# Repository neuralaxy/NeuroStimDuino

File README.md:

# NeuroStimDuino
An open source neurostimulator for students, researchers, and hobbyists interested in neuroscience

## Update for 2025 - NeuroStimDuino v3.0  launched!! :boom: :boom: 💫
Hello NeuroStim Enthusiats!! Its been a while....over the last year, we have been busy revising the design of NeuroStimDuino. The main reason for modifying NSDuino2.1 was that one of its crucial components, the high voltage DC-DC converter NMT0572SC from Murata has now became obsolete and out of circulation. Sadly, there was no alternative component that could take its place and we spend months trying to find a replacement. 

Finally we had a breakthrough, and we found another DC-DC converter IH0524 from XP Power. We had to redesign the board slightly to incorporate this Converter. But the *downside* is that the new converter only allows a compliance voltage of 35V instead of 60V available in the previous versions. How will this effect your experiments? Well, it means that now you will have to take extra effort in minimizing the skin impedance to deliver higher currents. But we have tried stimulating our arm muscles using this newer version, and it is just as effective as before. And we highly recommend using hydrogel electrodes, as we have suggested before in the [Zucchini](https://www.crowdsupply.com/neuralaxy/neurostimduino/updates/tips-on-electrode-placement) experiment. 

On the *upside*, while we were redesigning the board, we replaced the manual High Voltage slide switch with an electronic switch (see below). So now, you don't have to worry about turning ON the high voltage switch before activating the stimulator. Whenever you give the STIM command, the microcontroller will automatically turn ON the high voltage supply and once the stimulation is turned off, the high voltage supply is automatically turned off. Another benefit of adding the electronic switch is that it will minimize power consumption, since the high-voltage supply doesn't need to be always ON. Now that's smart😎.

All the other features from NSDuino2.1, like ramping stimulation intensity, touchproof conenctors, etc. have been carried over to NSDuino3.0. Late in September 2025, we launched NeuroStimDuino v3.0 abd shipped out the first batch to our distributor Mouser. A big shout out to 📢 CrowdSupply and Mouser for consistently supporting us over the years. Some of you might have already received the newer version. Try it and let us know how it goes.  

## Important update for 2023
In January 2023 we have launched NeuroStimDuino v2.1, which comes with additional features and improved functionality than its predecessor NeuroStimDuino v1.0. 

Here is a list of important upgrades for NeuroStimDuino v2.1 (NSDuino2.1): 
* Choosing between symmetrical and asymmetrical waveform shapes is now done entirely in software. In NeuroStimDuino v1.0, to switch from symmetrical to asymmetrical waveform, you had to change the jumper (J5, J6) as well as call the `SYMM` command. In NSDuino2.1, its handled entirely by software and the jumpers have been removed. In the default asymmetrical output mode, the anodic phase's amplitude is half of cathodic phase's amplitude and the duration of anodic phase is double that of the cathodic phase (to ensure charge balance). This ratio can be changed by modifying the firmware.

* NSDuino2.1's I<sup>2</sup>C address is now stored on EEPROM. So, whenever you assign a new I<sup>2</sup>C address to NSDuino2.1 using the `ADDR` command, it will get stored permanently and will be recalled at power-on reset. This is especially helpful when communicating with multiple NeuroStimDuinos. In NeuroStimDuino v1.0, the address would reset to the default value (0x1A) everytime the board was turned on and you would have to painstakingly re-assign the new addresses each time. With NSDuino2.1 the new address only needs to be set once and it will store it on-board its EEPROM.

* Many of NeuroStimDuino v1.0 users (who are acutally scientists!!) have asked whether it is possible to ramp up and down the stimulation intensity? Ramping is used in neurostimulation research to avoid painful sensations allow smoother transitions between movements when applying electrical stimulation. With NSDuino2.1, we have also expanded our software (Arduino) library and now provide the option to Ramp Up and Down the stimulation intentsity. When you enable ramping by using the command `RAMP 1`, the stimulation intensity will gradually increase from 0 to the desired level over a 1 second interval. At the end of stimulation, the stimulation intensity will gradually decrease to zero over a 1 second interval. There are some caveats to using ramping: 
  * In the scientific literature, ramping is usually done by increasing/decreasing the current amplitude. While this is doable, by changing the counts of our on-board digital potentiometer, it would require multiple SPI calls between the MCU and potentiometer which will introduce delays. Instead, we are performing ramping by gradually increasing the stimulation pulse-width. This is handled entirely by the MCU and hence it is more accurate. Additionally, it has the same effect as changing the stimulation current, so it won't affect the outcomes of your experiments. Refer to the below gif to understand how ramping essentially works:

  * Currently, ramping only works for finite stimulation intervals. This means the `Stim Indefinitely` flag of the `STIM` command must be set to `FALSE`. An example code snippet is as follows:
  
  ```
  RAMP 1          // Turn ON ramping on channels 1 & 2
  STIM 1 5 0      // Stimulate on channel 1 for 5 sec, stim indefinitely flag = 0
  RAMP 0          // Turn OFF ramping on channels 1 & 2
  ```
  * Ramping can also be deployed in NeuroStimDuino v1.0. This would require a firmware update. We will post an upgraded firmware for NeuroStimDuino v1.0 on our repository in a few weeks time. Feel free to reach out to us for any queries regarding ramping

* Additional minor modifications:
  * We removed the bi-color(red/green) LEDs to indicate when channels 1 and 2 are stimulating, with regular monocolor LEDs. These still function in the same way

  * We changed the onboard cable connectors for Channels 1 & 2 with new ones that are compatible with our stimulation cables and you no longer need to remove the cable shroud or sheath cover. This will hopefully help reduce the hassle during setup and the touchproof connectors will offer additional safety during use.

# Getting Started Tutorial for NeuroStimDuino v2.1
**_Important:_** For instructions on getting started with NeuroStimDuino v1.0, please click [here](https://github.com/neuralaxy/NeuroStimDuino/blob/main/NeuroStimDuino%20v1.0%20Getting%20Started.md#getting-started-tutorial-for-neurostimduino-v10)

* To get started, first and foremost familiarize yourself with NeuroStimDuino pinout and board layout below:

* If you have ordered the NeuroStimDuino board (without the accessory pack), then you will have received the following components.

* You also need to order a pair of hydrogel electrodes (from any retail vendor) if you plan to stimulate a fake muscle (such as a [Zucchini](https://www.crowdsupply.com/neuralaxy/neurostimduino/updates/tips-on-electrode-placement)) or for your research.

* Finally, before you begin, please remember to review the **safety guidelines** listed at the [end](https://github.com/neuralaxy/NeuroStimDuino/blob/main/README.md#important-safety-guidelines) of this tutorial and follow the recommendations mentioned therein.  

## Hardware Setup
* The battery holder included requires two 18650 Li-ion batteries (not included) to be connected in series. The battery holder allows the batteries to be oriented in series or parallel connection. Unfortunately, the battery holders we shipped only have Chinese labels to indicate the series or parallel oritentation. Make sure you connect the batteries in series (as shown below) and not in parallel. Alternately, you can power NeuroStimDuino using your own battery source between 6-20V. We do not recommend powering NeuroStimDuino using an AC-DC adapter. However, if you must use an adapter, then you need an adapter with atleast 2 Amps output rating

* The High-Voltage Power Switch S3 turns ON/OFF the +/-72V DC-DC converter (NMT0572SC). When using NeuroStimDuino for the first time we recommend starting with the switch in OFF position. Afterwards, once you are ready to stimulate then flip the switch ON. That way even if you accidentally turn ON the stimulation, it will not have any effect because the high-voltage source will be OFF. Plus it will also help extend battery life. 

* To control NeuroStimDuino using an Arduino Due or Mega, stack NeuroStimDuino on top of the Arduino board by aligning the hearder pins, as shown below.

* Once the hardware setup is complete, the amber or yellow Emergency-OFF LED will remain continuously ON. Also TEST_LED1 and TEST_LED2 will start blinking at a rate of 5 blinks per sec.

## Software Setup
* Next, you will need to download the latest version of our [Arduino library](https://github.com/neuralaxy/NeuroStimDuino/tree/main/Software/NeuroStimDuino). Read the full update [here](https://www.crowdsupply.com/neuralaxy/neurostimduino/updates/arduino-library-released) and remember to install the [SerialCommands library] (https://github.com/ppedro74/Arduino-SerialCommands) from Pedro Pereira. Next, open the example code [NeuroStimDuino_SerialControl.ino](Software/NeuroStimDuino/examples/NeuroSimDuino_SerialControl/NeuroSimDuino_SerialControl.ino) in the Arduino IDE. Then, zip the [NeuroStimDuino](Software/NeuroStimDuino/) directory and add it as a library through "Sketch->Include Lirary->Add .ZIP Library...". Finally, compile the example code and upload it onto the Arduino. 

* To write instructions to control NeuroStimDuino, you will use the Serial terminal that is in-built Arduino IDE (Tools > Serial Monitor). Once you open the Serial Monitor, set the baudrate to 115200 bps and add "CR+LF" at the end of each command. When you power either the Arduino or NeuroStimDuino board via the DC plug, you will see test LEDs 1 & 2 flashing on the NeuroStimDuino board. These LEDs are flashing with the default stimulation frequency of 10Hz. Now you can enter some example commands into the Serial Monitor, one command at a time and then press enter.

* After uploading the example code NeuroStimDuino_SerialControl.ino and making the connections as above, when you first open the Serial terminal you will see the following welcome message. This mean that a successful connection between Arduino and NeuroStimDuino has been established. It will also give a readout of the current stimulation parameters for each channel. 

* You can type in some example commands into Serial Monitor and change the settings for the stimulator (type one statement at a time). Also, the commands are case-sensitive, so type it in all caps. 
```
FREQ 1 20        // This will set Channel 1's frequency at 20Hz. You will see the TEST LED1 blink at this new frequency
FREQ 2 50        // This will set Channel 2's frequency at 50Hz. You will see the TEST LED1 blink at this new frequency
AMPL 1 15        // Set Channel 1 intensity 15mA
DURN 1 500       // Set Channel 1 pulse duration at 500 uSec
ENAB 1 1         // This will enable Channel 1 of the stimulation. By default, both channels are enabled at reset
STIM 1 20 0      // This command will turn on stimulation on Channel 1 for 20 seconds. Ensure that the High Voltage Power Switch is ON. 
                 // You will see a Red-Green LED (labelled Ch. 1) blink  very briefly (for 500us), every time the stimulation is generated (i.e, 20  times/sec)
```

## Moving forward

* This completes this introductory tutorial. From here on, if you would like to connect cables and electrodes and actuatlly stimulate a fake Zucchini muscle, then follow the setup instructions shown in our [April Update](https://www.crowdsupply.com/neuralaxy/neurostimduino/updates/tips-on-electrode-placement) published on CrowdSupply. 

* If you want connect multiple NeuroStimDuinos together and control them using a single Arduino, then look up the steps and instructions posted [earlier](https://www.crowdsupply.com/neuralaxy/neurostimduino/updates/controlling-multiple-neurostimduinos-on-a-single-i2c-bus). Note that with NeuroStimDuino_v2.1, when you change the board's I<sup>2</sup>C using the `ADDR` command, the new address is saved on-baord its EEPROM and will be recalled even after reset. It is the User's responsiblity to reset the default I<sup>2</sup>C to `0x1A` if they wish to. 
 
* <br />**One important change** required in hardware when stacking 2 or more NeuroStimDuinos is to disconnect pins 5 & 6 on JP3. Another way to identify these pins is that they normally connect with PWM pins 9 and 10 on Arduino Due or Mega. The reason for this is that these pins can also be used to drive TEST_LED1 and TEST_LED2 of NeuroStimDuino. Therefore, if you connect them together on 2 NeuroStimDuinos, the LEDs will not function properly and can be confusing. Hence, to avoid any cross-talk, its best to fold these pins out of the way as shown below.

* We hope you enjoy tinkering with NeuroStimDuino and use it for all your neuroscience experiments. If you face any issue with the device or are stuck anytime, feel free to write to us on contactus@neuralaxy.com or submit an issue here. 

## Important safety guidelines:
* NeuroStimDuino is not an FDA approved product for clinical use and it is intended for **RESEARCH PURPOSES ONLY**. 
* NeuroStimDuino is not intended for human use or animal use, without receiving prior approval from a local ethics committee such as Institutional Review Boards and Institutional Animal Care and Use Committees  
* Under no circumstances, should the stimulation electrodes be placed across the chest or close to the heart
* NeuroStimDuino requires an external DC input voltage from 6-20V to operate. We **strongly** recommend to use an external battery for this and avoid the use of an AC adapter or anything that's plugged into the AC mains
--->

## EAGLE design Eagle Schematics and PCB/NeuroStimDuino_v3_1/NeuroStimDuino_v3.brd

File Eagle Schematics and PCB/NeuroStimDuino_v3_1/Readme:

Eagle schematics, BOM and assembly files for version 3.0 of NeuroStimDuino

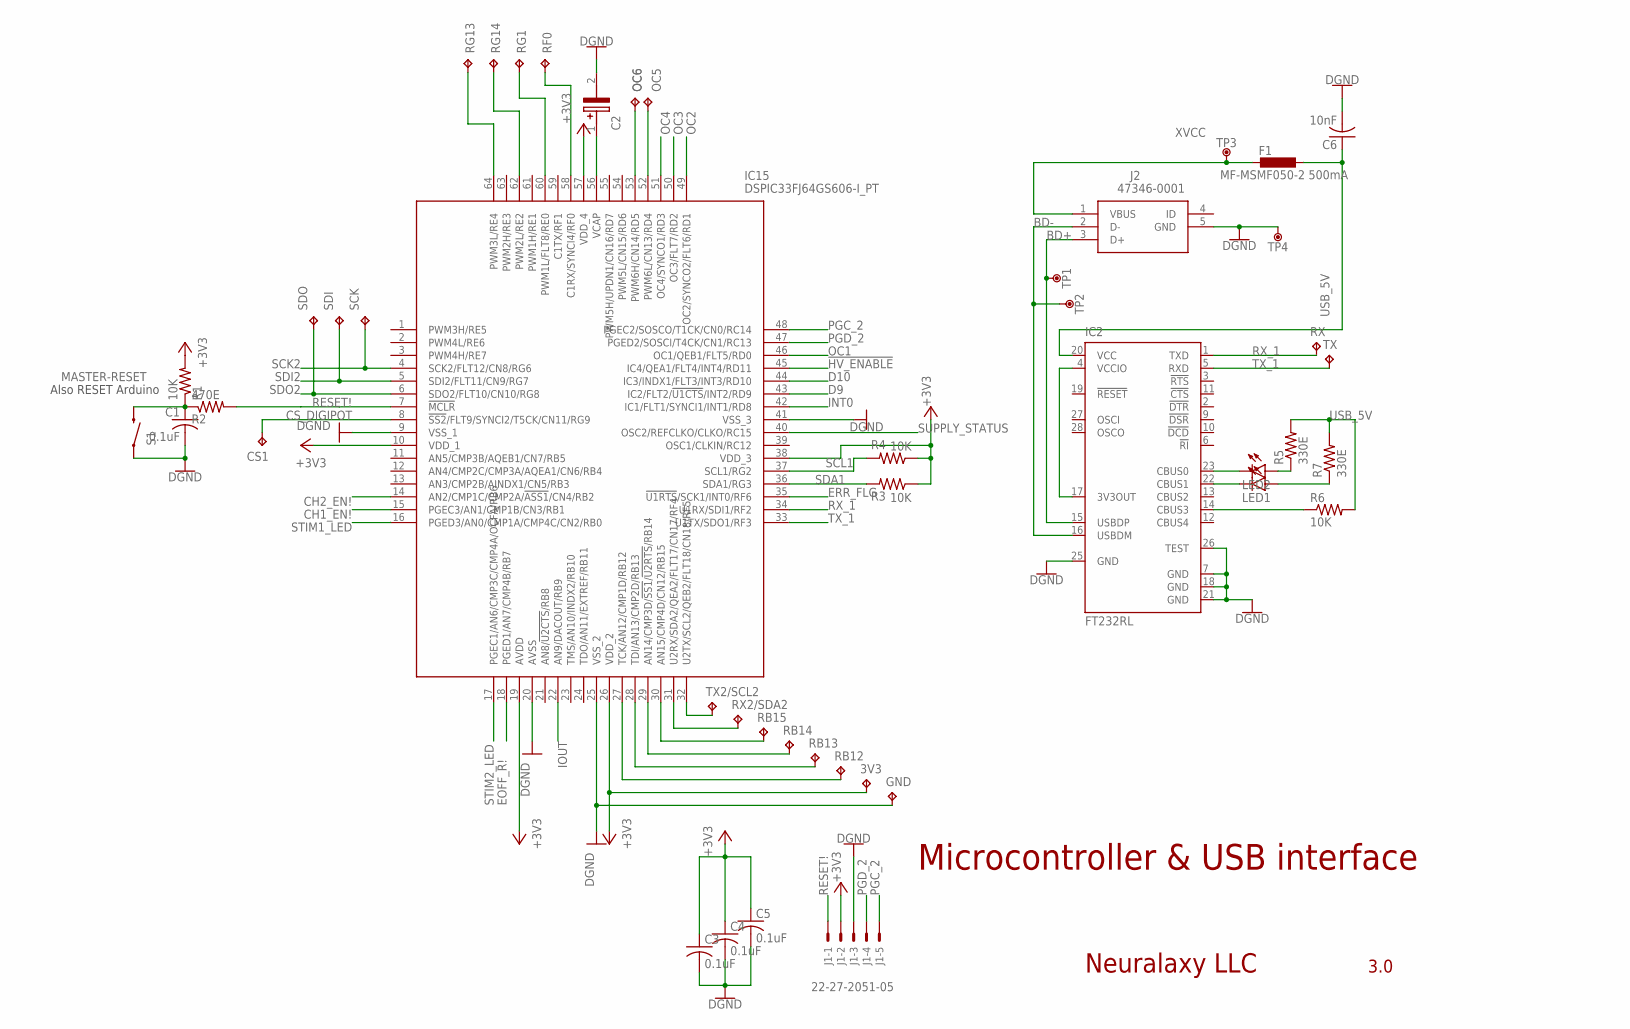
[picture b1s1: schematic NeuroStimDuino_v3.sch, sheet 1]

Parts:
3V3: TPTP08R; TP08R
/OC5: TPTP08R; TP08R
C1: 0.1uF; C0805
C2: F971C475MAAHT3; CAPPM3216X180N
C3, C4, C5: 0.1uF; C1206
C6: 10nF; C1206
CS1: TPTP08R; TP08R
F1: MF-MSMF050-2 500mA; L1812
GND: TPTP08R; TP08R
IC2: FT232RL; SSOP28
IC15: DSPIC33FJ64GS606-I_PT; QFP50P1200X1200X120-64N
J1: 22-27-2051-05; 6410-05
J2: 47346-0001
LED1, LED2: LEDCHIPLED_1206; CHIPLED_1206
OC6: TPTP08R; TP08R
R1: 10K; R0805
R2: 470E; R0805
R3, R4, R6: 10K; R1206
R5, R7: 330E; R1206
RB12, RB13, RB14, RB15: TPTP08R; TP08R
RF0: TPTP08R; TP08R
RG1, RG13, RG14: TPTP08R; TP08R
RX: TPTP20R; TP20R
RX2/SDA2: TPTP08R; TP08R
S1: SWITCH-MOMENTARY-2SMD; TACTILE_SWITCH_SMD
SCK: TPTP10R; TP10R
SDI: TPTP10R; TP10R
SDO: TPTP10R; TP10R
TP1, TP2, TP3, TP4: DNP; TP-1.00MM
TX: TPTP20R; TP20R
TX2/SCL2: TPTP08R; TP08R

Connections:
!HV_ENABLE: IC15.45 (IC4/QEA1/FLT4/INT4/RD11); also elsewhere on the board
+3V3: 3V3.TP, C3.1, C4.1, C5.1, IC15.10 (VDD_1), IC15.19 (AVDD), IC15.26 (VDD_2), IC15.38 (VDD_3), IC15.57 (VDD_4), J1.2, R1.2, R3.1, R4.1; also elsewhere on the board
BD+: IC2.15 (USBDP), J2.3 (D+), TP1.X
BD-: IC2.16 (USBDM), J2.2 (D-), TP2.X
CH1_EN!: IC15.15 (PGEC3/AN1/CMP1B/CN3/RB1); also elsewhere on the board
CH2_EN!: IC15.14 (AN2/CMP1C/CMP2A/!ASS1!/CN4/RB2); also elsewhere on the board
CS_DIGIPOT: CS1.TP, IC15.8 (!SS2!/FLT9/SYNCI2/T5CK/CN11/RG9); also elsewhere on the board
D9: IC15.43 (IC2/FLT2/!U1CTS!/INT2/RD9); also elsewhere on the board
D10: IC15.44 (IC3/INDX1/FLT3/INT3/RD10); also elsewhere on the board
EOFF_R!: IC15.18 (PGED1/AN7/CMP4B/RB7); also elsewhere on the board
ERR_FLG: IC15.35 (!U1RTS!/SCK1/INT0/RF6); also elsewhere on the board
GND: C1.2, C2.2 (-), C3.2, C4.2, C5.2, C6.2, GND.TP, IC2.7 (GND), IC2.18 (GND), IC2.21 (GND), IC2.25 (GND), IC2.26 (TEST), IC15.9 (VSS_1), IC15.20 (AVSS), IC15.25 (VSS_2), IC15.41 (VSS_3), J1.3, J2.5 (GND), S1.1, TP4.X; also elsewhere on the board
INT0: IC15.42 (IC1/FLT1/SYNCI1/INT1/RD8); also elsewhere on the board
IOUT: IC15.22 (AN9/DACOUT/RB9); also elsewhere on the board
MASTER-RESET: C1.1, R1.1, R2.1, S1.3 (2); also elsewhere on the board
unnamed: C2.1 (+), IC15.56 (VCAP)
unnamed: IC15.32 (U2TX/SCL2/QEB2/FLT18/CN18/RF5), TX2/SCL2.TP
unnamed: IC15.31 (U2RX/SDA2/QEA2/FLT17/CN17/RF4), RX2/SDA2.TP
unnamed: IC15.30 (AN15/CMP4D/CN12/RB15), RB15.TP
unnamed: IC15.29 (AN14/CMP3D/!SS1!/!U2RTS!/RB14), RB14.TP
unnamed: IC15.28 (TDI/AN13/CMP2D/RB13), RB13.TP
unnamed: IC15.27 (TCK/AN12/CMP1D/RB12), RB12.TP
unnamed: IC15.58 (C1RX/SYNCI4/RF0), RF0.TP
unnamed: IC15.60 (PWM1L/FLT8/RE0), RG1.TP
unnamed: IC15.62 (PWM2L/RE2), RG14.TP
unnamed: IC15.64 (PWM3L/RE4), RG13.TP
unnamed: IC2.4 (VCCIO), IC2.17 (3V3OUT)
unnamed: IC2.23 (CBUS0), LED2.C
unnamed: LED2.A, R5.1
unnamed: LED1.A, R7.1
unnamed: IC2.22 (CBUS1), LED1.C
unnamed: IC2.14 (CBUS3), R6.1
OC1: IC15.46 (OC1/QEB1/FLT5/RD0); also elsewhere on the board
OC2: IC15.49 (OC2/SYNCO2/FLT6/RD1); also elsewhere on the board
OC3: IC15.50 (OC3/FLT7/RD2); also elsewhere on the board
OC4: IC15.51 (OC4/SYNCO1/RD3); also elsewhere on the board
OC5: /OC5.TP, IC15.52 (PWM6L/CN13/RD4)
OC6: IC15.53 (PWM6H/CN14/RD5), OC6.TP
PGC_2: IC15.48 (PGEC2/SOSCO/T1CK/CN0/RC14), J1.5
PGD_2: IC15.47 (PGED2/SOSCI/T4CK/CN1/RC13), J1.4
RESET!: IC15.7 (!MCLR), J1.1, R2.2
RX_1: IC2.1 (TXD), IC15.34 (U1RX/SDI1/RF2), RX.TP
SCK2: IC15.4 (SCK2/FLT12/CN8/RG6), SCK.TP; also elsewhere on the board
SCL1: IC15.37 (SCL1/RG2), R4.2; also elsewhere on the board
SDA1: IC15.36 (SDA1/RG3), R3.2; also elsewhere on the board
SDI2: IC15.5 (SDI2/FLT11/CN9/RG7), SDI.TP; also elsewhere on the board
SDO2: IC15.6 (SDO2/FLT10/CN10/RG8), SDO.TP; also elsewhere on the board
STIM1_LED: IC15.16 (PGED3/AN0/CMP1A/CMP4C/CN2/RB0); also elsewhere on the board
STIM2_LED: IC15.17 (PGEC1/AN6/CMP3C/CMP4A/OCFA/RB6); also elsewhere on the board
SUPPLY_STATUS: IC15.40 (OSC2/REFCLKO/CLKO/RC15); also elsewhere on the board
TX_1: IC2.5 (RXD), IC15.33 (U1TX/SDO1/RF3), TX.TP
USB_5V: C6.1, F1.1, IC2.20 (VCC), R5.2, R6.2, R7.2; also elsewhere on the board
XVCC: F1.2, J2.1 (VBUS), TP3.X

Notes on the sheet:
Microcontroller & USB interface
Also RESET Arduino
3.0
Neuralaxy LLC

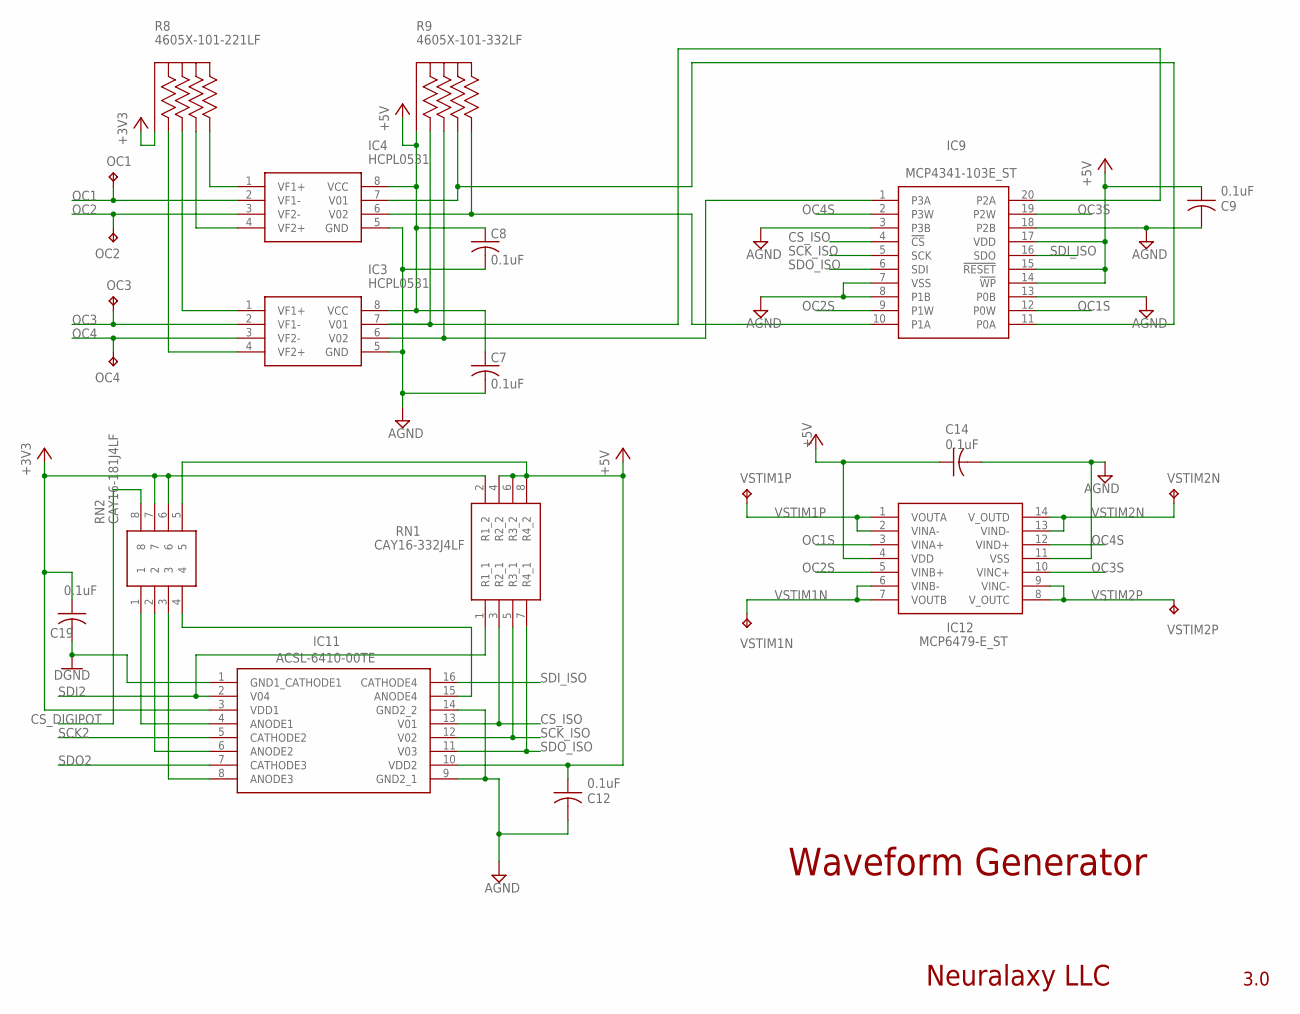
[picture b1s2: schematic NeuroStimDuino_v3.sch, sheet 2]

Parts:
C7, C8, C9, C12, C14, C19: 0.1uF; C1206
IC3, IC4: HCPL0531; SOIC127P594X363-8N
IC9: MCP4341-103E_ST; SOP65P640X120-20N
IC11: ACSL-6410-00TE; SOIC127P599X152-16N
IC12: MCP6479-E_ST; SOP65P640X120-14N
OC1, OC2: TPTP08R; TP08R
OC3, OC4: TPTP10R; TP10R
R8: 4605X-101-221LF; BO_4605X
R9: 4605X-101-332LF; BO_4605X
RN1: CAY16-332J4LF; CAY16-J4
RN2: CAY16-181J4LF; CAY16181J4LF
VSTIM1N, VSTIM1P, VSTIM2N, VSTIM2P: TPTP08R; TP08R

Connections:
+3V3: C19.1, IC11.3 (VDD1), R8.1, RN1.2 (R1_2), RN2.6, RN2.7; also elsewhere on the board
+5V: C7.1, C8.1, C9.1, C12.1, C14.1, IC3.8 (VCC), IC4.8 (VCC), IC9.14 (!WP), IC9.15 (!RESET), IC9.17 (VDD), IC11.10 (VDD2), IC12.4 (VDD), R9.1, RN1.4 (R2_2), RN1.6 (R3_2), RN1.8 (R4_2), RN2.5; also elsewhere on the board
AGND: C7.2, C8.2, C9.2, C12.2, C14.2, IC3.5 (GND), IC4.5 (GND), IC9.3 (P3B), IC9.7 (VSS), IC9.8 (P1B), IC9.13 (P0B), IC9.18 (P2B), IC11.9 (GND2_1), IC11.14 (GND2_2), IC12.11 (VSS); also elsewhere on the board
CS_DIGIPOT: RN2.8; also elsewhere on the board
CS_ISO: IC9.4 (!CS), IC11.13 (V01), RN1.3 (R2_1)
GND: C19.2, IC11.1 (GND1_CATHODE1); also elsewhere on the board
unnamed: IC11.4 (ANODE1), RN2.1
unnamed: IC4.7 (V01), IC9.11 (P0A), R9.4
unnamed: IC4.6 (V02), IC9.10 (P1A), R9.5
unnamed: IC3.7 (V01), IC9.20 (P2A), R9.2
unnamed: IC3.6 (V02), IC9.1 (P3A), R9.3
unnamed: IC4.4 (VF2+), R8.4
unnamed: IC4.1 (VF1+), R8.5
unnamed: IC3.1 (VF1+), R8.3
unnamed: IC3.4 (VF2+), R8.2
unnamed: IC11.6 (ANODE2), RN2.2
unnamed: IC11.8 (ANODE3), RN2.3
unnamed: IC11.15 (ANODE4), RN2.4
OC1: IC4.2 (VF1-), OC1.TP; also elsewhere on the board
OC1S: IC9.12 (P0W), IC12.3 (VINA+)
OC2: IC4.3 (VF2-), OC2.TP; also elsewhere on the board
OC2S: IC9.9 (P1W), IC12.5 (VINB+)
OC3: IC3.2 (VF1-), OC3.TP; also elsewhere on the board
OC3S: IC9.19 (P2W), IC12.10 (VINC+)
OC4: IC3.3 (VF2-), OC4.TP; also elsewhere on the board
OC4S: IC9.2 (P3W), IC12.12 (VIND+)
SCK2: IC11.5 (CATHODE2); also elsewhere on the board
SCK_ISO: IC9.5 (SCK), IC11.12 (V02), RN1.5 (R3_1)
SDI2: IC11.2 (V04), RN1.1 (R1_1); also elsewhere on the board
SDI_ISO: IC9.16 (SDO), IC11.16 (CATHODE4)
SDO2: IC11.7 (CATHODE3); also elsewhere on the board
SDO_ISO: IC9.6 (SDI), IC11.11 (V03), RN1.7 (R4_1)
VSTIM1N: IC12.6 (VINB-), IC12.7 (VOUTB), VSTIM1N.TP; also elsewhere on the board
VSTIM1P: IC12.1 (VOUTA), IC12.2 (VINA-), VSTIM1P.TP; also elsewhere on the board
VSTIM2N: IC12.13 (VIND-), IC12.14 (V_OUTD), VSTIM2N.TP; also elsewhere on the board
VSTIM2P: IC12.8 (V_OUTC), IC12.9 (VINC-), VSTIM2P.TP; also elsewhere on the board

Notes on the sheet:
Waveform Generator
Neuralaxy LLC
3.0

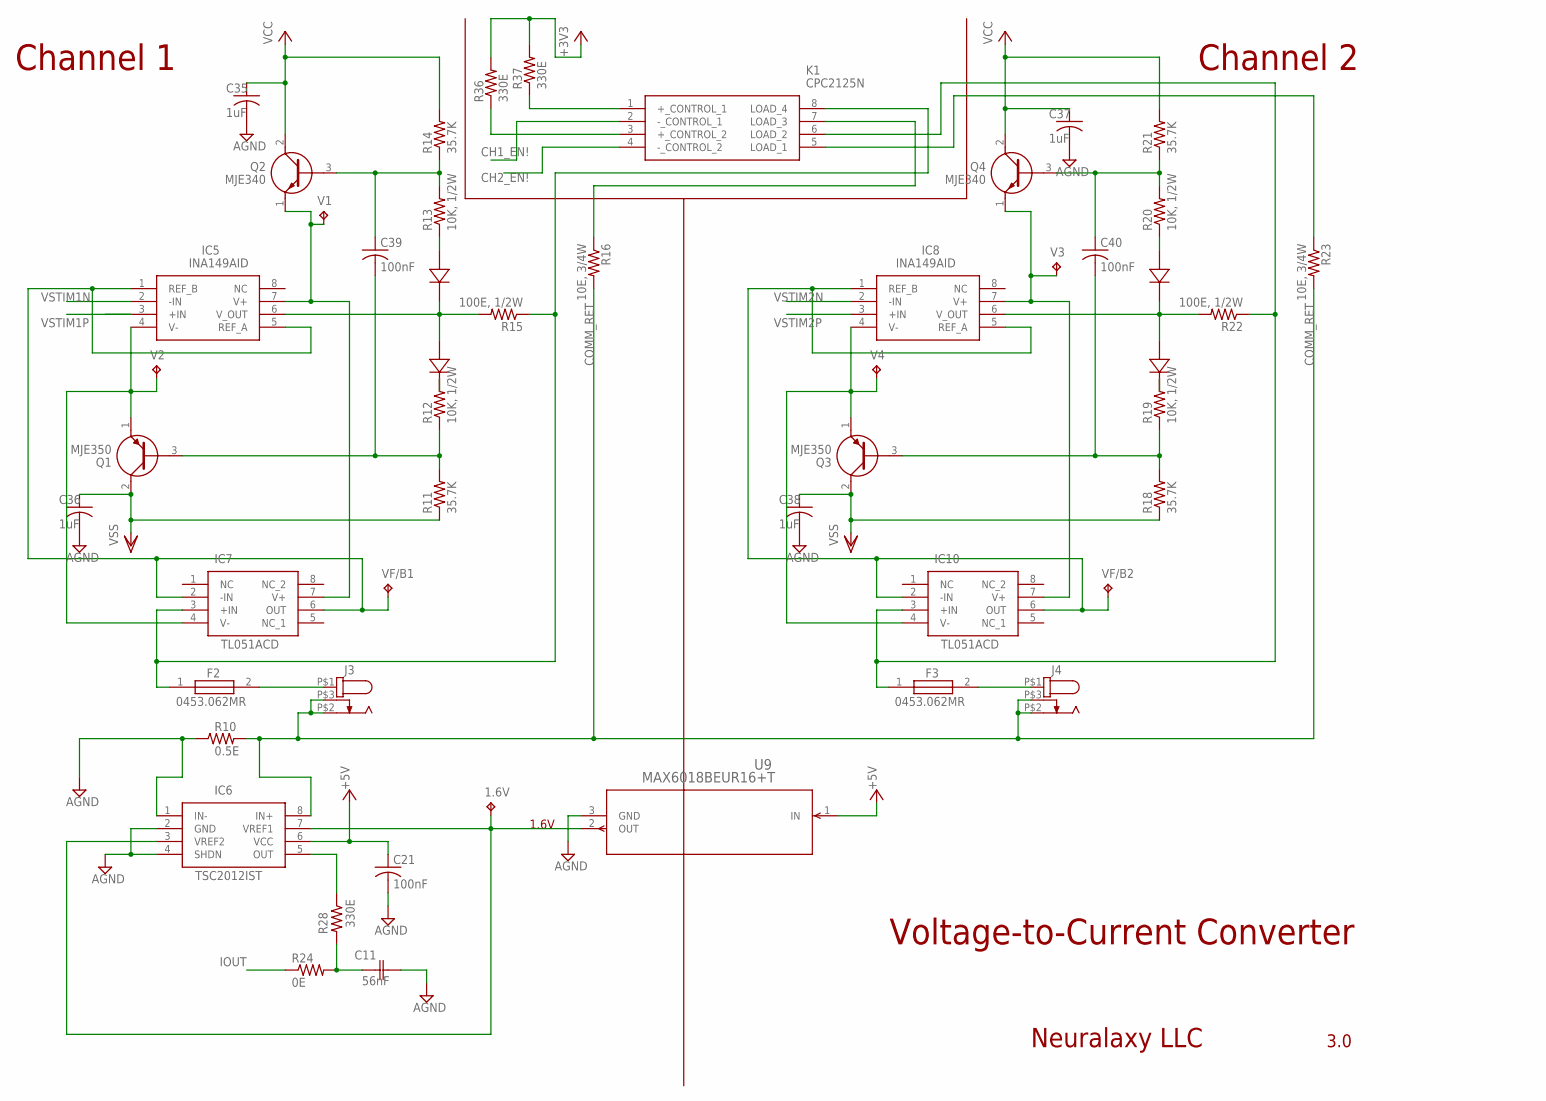
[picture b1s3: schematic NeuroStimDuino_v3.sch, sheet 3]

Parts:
1.6V: TPTP10R; TP10R
C11: 56nF; CAPC17595_87N_KEM
C21: 100nF; C1206
C35, C36, C37, C38: 1uF; C0805
C39, C40: 100nF; C0805K
D6, D7, D8, D9: GF1J-E3DO-214BA-L; DO-214BA-L
F2, F3: 0453.062MR; FUSC6127X294N
IC5, IC8: INA149AID; SOIC127P600X175-8N
IC6: TSC2012IST; SOP65P490X110-8N
IC7, IC10: OPA140AID; SOIC127P600X175-8N
J3, J4: DC_JACK_081BB-2103300; 081BB-2103300
K1: CPC2125N; SOP254P610X218-8N
Q1, Q3: MJE350; TO229P300X760X1364-3P
Q2, Q4: MJE340; TO229P290X760X1320-3P
R10: 0.5E; R1206
R11, R14, R18, R21: 35.7K; R1206
R12, R13, R19, R20: 10K, 1/2W; R1206
R15, R22: 100E, 1/2W; R1206
R16, R23: 10E, 3/4W; R1206
R24: 0E; R1206
R28: 330E; R0603
R36, R37: 330E; R1206
U9: MAX6018BEUR16+T; 21-0051H_MXM
V1, V2, V3, V4: TPTP10R; TP10R
VF/B1, VF/B2: TPTP10R; TP10R

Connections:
+3V3: R36.2, R37.2; also elsewhere on the board
+5V: C21.1, IC6.6 (VCC), U9.1 (IN); also elsewhere on the board
AGND: C11.2, C21.2, C35.2, C36.2, C37.2, C38.2, IC6.1 (IN-), IC6.2 (GND), IC6.4 (SHDN), R10.1, U9.3 (GND); also elsewhere on the board
CH1_EN!: K1.2 (-_CONTROL_1); also elsewhere on the board
CH2_EN!: K1.4 (-_CONTROL_2); also elsewhere on the board
COMM_RET: IC6.8 (IN+), J3.P$2 (2), J3.P$3 (3), J4.P$2 (2), J4.P$3 (3), R10.2, R16.2, R23.2
IOUT: R24.1; also elsewhere on the board
unnamed: K1.1 (+_CONTROL_1), R37.1
unnamed: K1.3 (+_CONTROL_2), R36.1
unnamed: IC6.5 (OUT), R28.1
unnamed: 1.6V.TP, IC6.3 (VREF2), IC6.7 (VREF1), U9.2 (OUT)
unnamed: C11.1, R24.2, R28.2
unnamed: IC5.4 (V-), IC7.4 (V-), Q1.1 (E), V2.TP
unnamed: IC5.1 (REF_B), IC5.5 (REF_A), IC7.2 (-IN), IC7.6 (OUT), VF/B1.TP
unnamed: C39.1, Q2.3 (B), R13.2, R14.1
unnamed: C39.2, Q1.3 (B), R11.2, R12.1
unnamed: D6.2, R13.1
unnamed: D7.1, R12.2
unnamed: D6.1, D7.2, IC5.6 (V_OUT), R15.2
unnamed: IC5.7 (V+), IC7.7 (V+), Q2.1 (E), V1.TP
unnamed: K1.7 (LOAD_3), R16.1
unnamed: F2.1, IC7.3 (+IN), K1.8 (LOAD_4), R15.1
unnamed: K1.5 (LOAD_1), R23.1
unnamed: F2.2, J3.P$1 (1)
unnamed: C40.1, Q4.3 (B), R20.2, R21.1
unnamed: C40.2, Q3.3 (B), R18.2, R19.1
unnamed: D8.2, R20.1
unnamed: D9.1, R19.2
unnamed: D8.1, D9.2, IC8.6 (V_OUT), R22.2
unnamed: IC8.1 (REF_B), IC8.5 (REF_A), IC10.2 (-IN), IC10.6 (OUT), VF/B2.TP
unnamed: IC8.7 (V+), IC10.7 (V+), Q4.1 (E), V3.TP
unnamed: IC8.4 (V-), IC10.4 (V-), Q3.1 (E), V4.TP
unnamed: F3.1, IC10.3 (+IN), K1.6 (LOAD_2), R22.1
unnamed: F3.2, J4.P$1 (1)
VCC: C35.1, C37.1, Q2.2 (C), Q4.2 (C), R14.2, R21.2; also elsewhere on the board
VSS: C36.1, C38.1, Q1.2 (C), Q3.2 (C), R11.1, R18.1; also elsewhere on the board
VSTIM1N: IC5.2 (-IN); also elsewhere on the board
VSTIM1P: IC5.3 (+IN); also elsewhere on the board
VSTIM2N: IC8.2 (-IN); also elsewhere on the board
VSTIM2P: IC8.3 (+IN); also elsewhere on the board

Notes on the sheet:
Voltage-to-Current Converter
Channel 1
Channel 2
1.6V
TSC2012IST
Neuralaxy LLC
3.0
TL051ACD

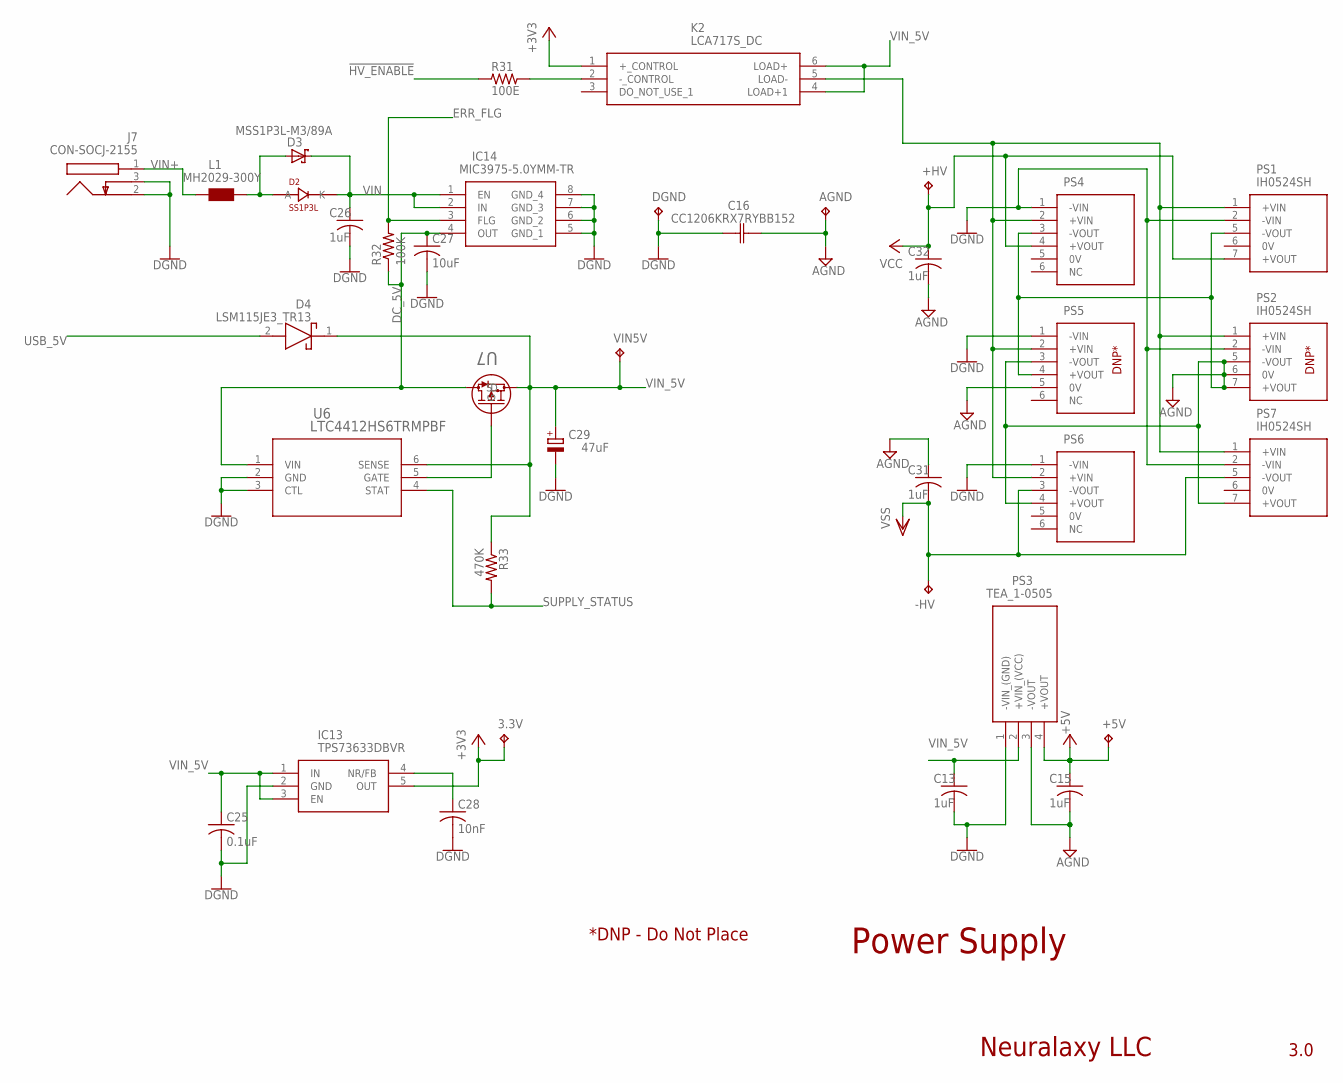
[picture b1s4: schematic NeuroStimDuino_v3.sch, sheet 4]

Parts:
3.3V: TPTP10R; TP10R
+5V: TPTP10R; TP10R
+HV: TPTP10R; TP10R
-HV: TPTP10R; TP10R
AGND: TPTP10R; TP10R
C13, C15, C26, C31, C32: 1uF; C0805
C16: CC1206KRX7RYBB152; CAP_CC1206_YAG
C25: 0.1uF; C1206
C27: 10uF; C0805
C28: 10nF; C1206
C29: 47uF; PANASONIC_D
D2: SS1P3L; DO220AAL
D3: MSS1P3L-M3/89A; MICROSMP
D4: LSM115JE3_TR13; DIOM5436X330N
DGND: TPTP10R; TP10R
IC13: TPS73633DBVR; SOT95P280X145-5N
IC14: MIC3975-5.0YMM-TR; SOP65P490X109-8N
J7: CON-SOCJ-2155; CONSOCJ2155
K2: LCA717S_DC; SOP254P952X470-6N
L1: MH2029-300Y; 0805
PS1, PS2, PS7: IH0524SH
PS3: TEA_1-0505; TEA10505
PS4, PS5, PS6: IH0524D
R31: 100E; R0805
R32: 100K; R1206
R33: 470K; R1206
U6: LTC4412HS6TRMPBF; TSOT-23_S6_ADI
U7: PMV48XP,215TO-236_SOT23_NEX-L; TO-236_SOT23_NEX-L
VIN5V: TPTP10R; TP10R

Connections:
!HV_ENABLE: R31.1; also elsewhere on the board
+3V3: 3.3V.TP, IC13.5 (OUT), K2.1 (+_CONTROL); also elsewhere on the board
+5V: +5V.TP, C15.1, PS3.4 (+VOUT); also elsewhere on the board
AGND: AGND.TP, C15.2, C16.2, C31.1, C32.2, PS1.5 (-VOUT), PS2.5 (-VOUT), PS2.6 (0V), PS2.7 (+VOUT), PS3.3 (-VOUT), PS4.3 (-VOUT), PS5.3 (-VOUT), PS5.4 (+VOUT), PS5.5 (0V), PS6.4 (+VOUT), PS7.7 (+VOUT); also elsewhere on the board
DC_5V: C27.1, IC14.4 (OUT), R32.1, U6.1 (VIN), U7.3 (D)
ERR_FLG: IC14.3 (FLG), R32.2; also elsewhere on the board
GND: C13.2, C16.1, C25.2, C26.2, C27.2, C28.2, C29.-, DGND.TP, IC13.2 (GND), IC14.5 (GND_1), IC14.6 (GND_2), IC14.7 (GND_3), IC14.8 (GND_4), J7.2, J7.3, PS1.2 (-VIN), PS2.2 (-VIN), PS3.1 (-VIN_(GND)), PS4.1 (-VIN), PS5.1 (-VIN), PS6.1 (-VIN), PS7.2 (-VIN), U6.2 (GND), U6.3 (CTL); also elsewhere on the board
unnamed: C28.1, IC13.4 (NR/FB)
unnamed: K2.5 (LOAD-), PS1.1 (+VIN), PS2.1 (+VIN), PS4.2 (+VIN), PS5.2 (+VIN), PS6.2 (+VIN), PS7.1 (+VIN)
unnamed: U6.5 (GATE), U7.1 (G)
unnamed: K2.2 (-_CONTROL), R31.2
unnamed: D2.P$2 (A), D3.A, L1.1
SUPPLY_STATUS: R33.2, U6.4 (STAT); also elsewhere on the board
USB_5V: D4.2 (A); also elsewhere on the board
VCC: +HV.TP, C32.1, PS1.7 (+VOUT), PS4.4 (+VOUT); also elsewhere on the board
VIN: C26.1, D2.P$1 (K), D3.K (C), IC14.1 (EN), IC14.2 (IN); also elsewhere on the board
VIN+: J7.1, L1.2
VIN_5V: C13.1, C25.1, C29.+, D4.1 (K), IC13.1 (IN), IC13.3 (EN), K2.4 (LOAD+1), K2.6 (LOAD+), PS3.2 (+VIN_(VCC)), R33.1, U6.6 (SENSE), U7.2 (S), VIN5V.TP; also elsewhere on the board
VSS: -HV.TP, C31.2, PS6.3 (-VOUT), PS7.5 (-VOUT); also elsewhere on the board

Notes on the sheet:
Power Supply
Neuralaxy LLC
3.0
DNP*
*DNP - Do Not Place

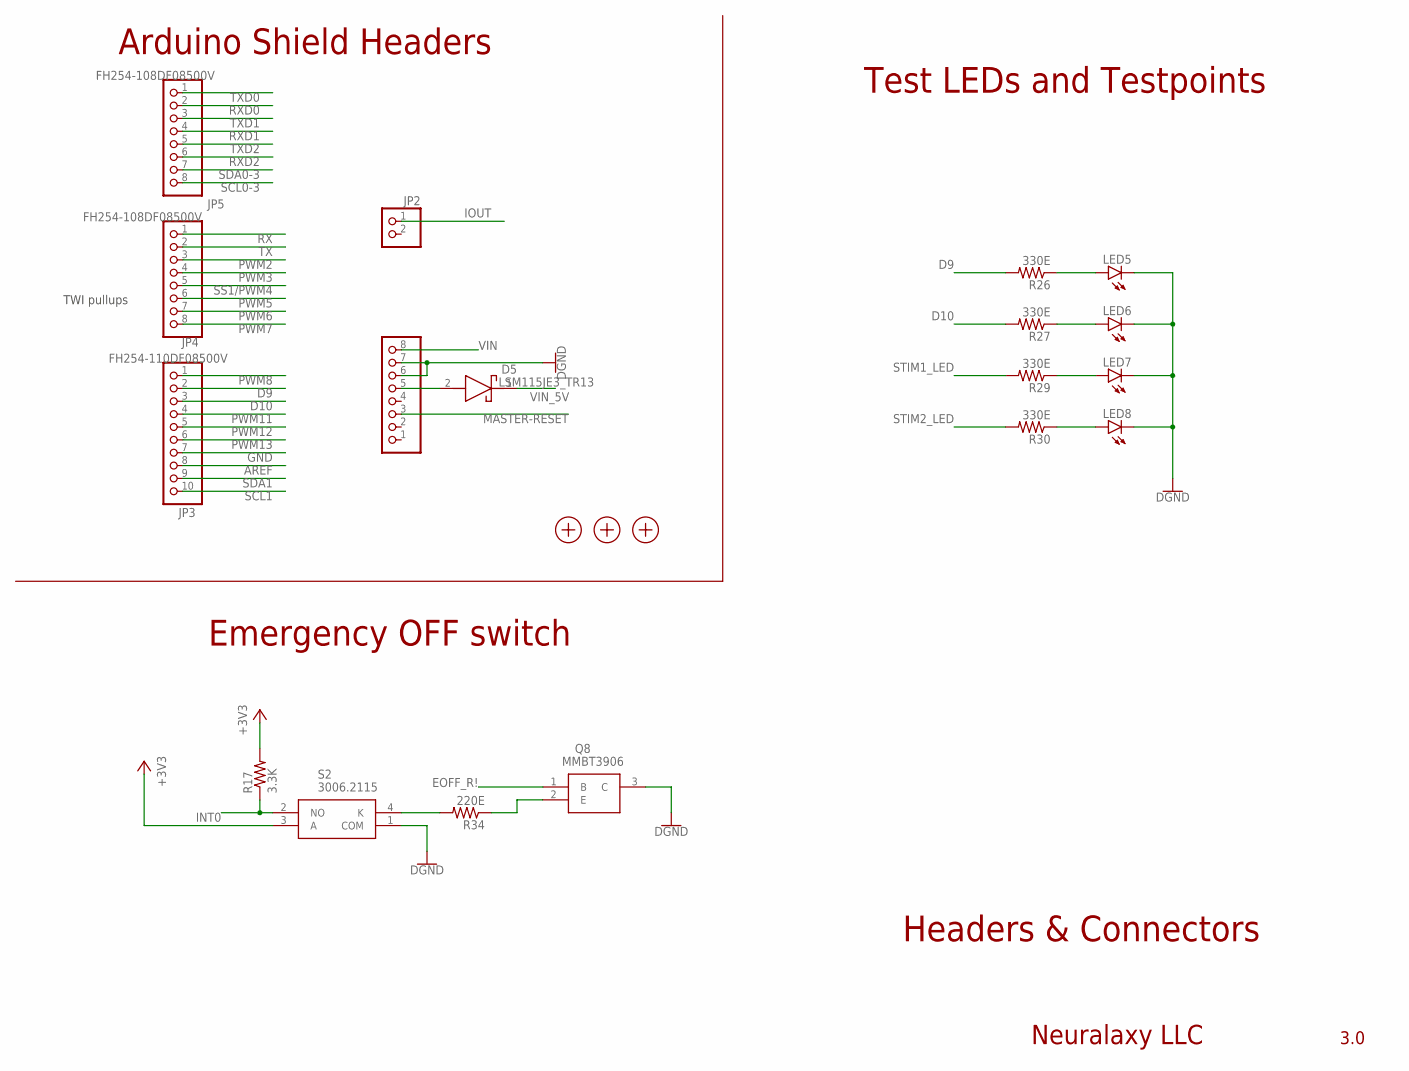
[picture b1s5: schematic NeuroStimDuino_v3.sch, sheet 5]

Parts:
D5: LSM115JE3_TR13; DIOM5436X330N
JP2: PINHD-1X2; 1X02
JP3: FH254-110DF08500V; 1X10
JP4, JP5, JP6: FH254-108DF08500V; 1X08
LED5, LED6, LED7, LED8: LEDCHIPLED_1206; CHIPLED_1206
Q8: MMBT3906; SOT95P240X120-3N
R17: 3.3K; R1206
R26, R27, R29, R30: 330E; R0603
R34: 220E; R1206
S2: 3006.2115; 30062115
U$1, U$2, U$3: FIDUCIALMOUNT; FIDUCIA-MOUNT

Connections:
+3V3: R17.2, S2.3 (A); also elsewhere on the board
AREF: JP3.8
D9: JP3.2, R26.2; also elsewhere on the board
D10: JP3.3, R27.2; also elsewhere on the board
EOFF_R!: Q8.1 (B); also elsewhere on the board
GND: JP3.7, JP6.6, JP6.7, LED5.C, LED6.C, LED7.C, LED8.C, Q8.3 (C), S2.1 (COM); also elsewhere on the board
INT0: R17.1, S2.2 (NO); also elsewhere on the board
IOUT: JP2.1; also elsewhere on the board
MASTER-RESET: JP6.3; also elsewhere on the board
unnamed: D5.2 (A), JP6.5
unnamed: R34.2, S2.4 (K)
unnamed: Q8.2 (E), R34.1
unnamed: LED8.A, R30.1
unnamed: LED7.A, R29.1
unnamed: LED6.A, R27.1
unnamed: LED5.A, R26.1
PWM2: JP4.3
PWM3: JP4.4
PWM5: JP4.6
PWM6: JP4.7
PWM7: JP4.8
PWM8: JP3.1
PWM11: JP3.4
PWM12: JP3.5
PWM13: JP3.6
RX: JP4.1
RXD0: JP5.2
RXD1: JP5.4
RXD2: JP5.6
SCL0-3: JP5.8
SCL1: JP3.10; also elsewhere on the board
SDA0-3: JP5.7
SDA1: JP3.9; also elsewhere on the board
SS1/PWM4: JP4.5
STIM1_LED: R29.2; also elsewhere on the board
STIM2_LED: R30.2; also elsewhere on the board
TX: JP4.2
TXD0: JP5.1
TXD1: JP5.3
TXD2: JP5.5
VIN: JP6.8; also elsewhere on the board
VIN_5V: D5.1 (K); also elsewhere on the board

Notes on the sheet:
Headers & Connectors
TWI pullups
Arduino Shield Headers
Test LEDs and Testpoints
Emergency OFF switch
Neuralaxy LLC
3.0

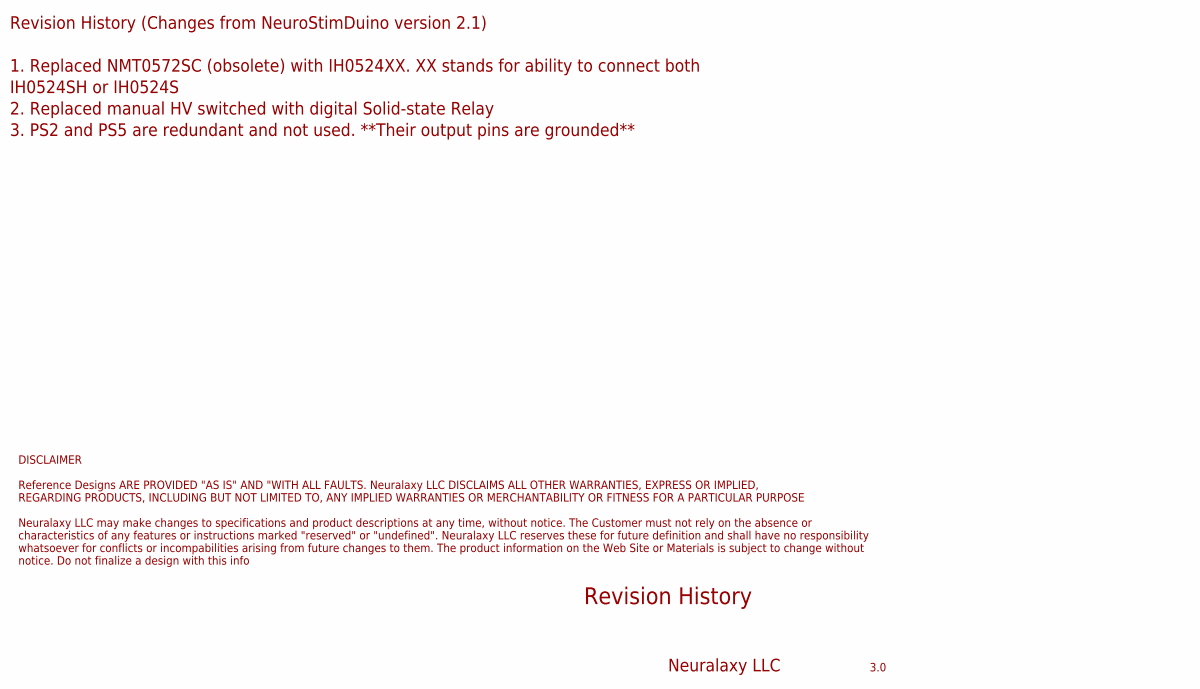
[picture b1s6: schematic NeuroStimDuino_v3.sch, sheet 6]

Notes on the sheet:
Revision History
Revision History (Changes from NeuroStimDuino version 2.1) 1. Replaced NMT0572SC (obsolete) with IH0524XX. XX stands for ability to connect both IH0524SH or IH0524S 2. Replaced manual HV switched with digital Solid-state Relay 3. PS2 and PS5 are redundant and not used. **Their output pins are groun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
DISCLAIMER Reference Designs ARE PROVIDED "AS IS" AND "WITH ALL FAULTS. Neuralaxy LLC DISCLAIMS ALL OTHER WARRANTIES, EXPRESS OR IMPLIED, REGARDING PRODUCTS, INCLUDING BUT NOT LIMITED TO, ANY IMPLIED WARRANTIES OR MERCHANTABILITY OR FITNESS FOR A PARTICULAR PURPOSE Neuralaxy LLC may make changes to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
Neuralaxy LLC
3.0

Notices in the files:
parts and their libraries:
Arduino-utility: Copyright (c) 2016-2017 Arduino LLC.  All right reserved.
DC_power_jack2_35mm: Copyright: Würth Elektronik
rc-master-smd: Copyright (C) 2007, Bob Starr
COPYRIGHT: Copyright (C) 2018 Accelerated Designs. All rights reserved
